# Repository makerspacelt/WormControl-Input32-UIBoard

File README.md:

---

WormControl Input32 User Interface board

NOTE: This is only a prototype now, so things might not work and everything might change 

Dev NOTE: before commit, run `./kibot.sh` to regenerate documentation, bom, gerbers and other assets.

* [schematics.pdf](gen/schematics.pdf)
* [pcb.pdf with dimensions](gen/pcb.pdf)
* [ibom.html](gen/single/ibom.html)

---

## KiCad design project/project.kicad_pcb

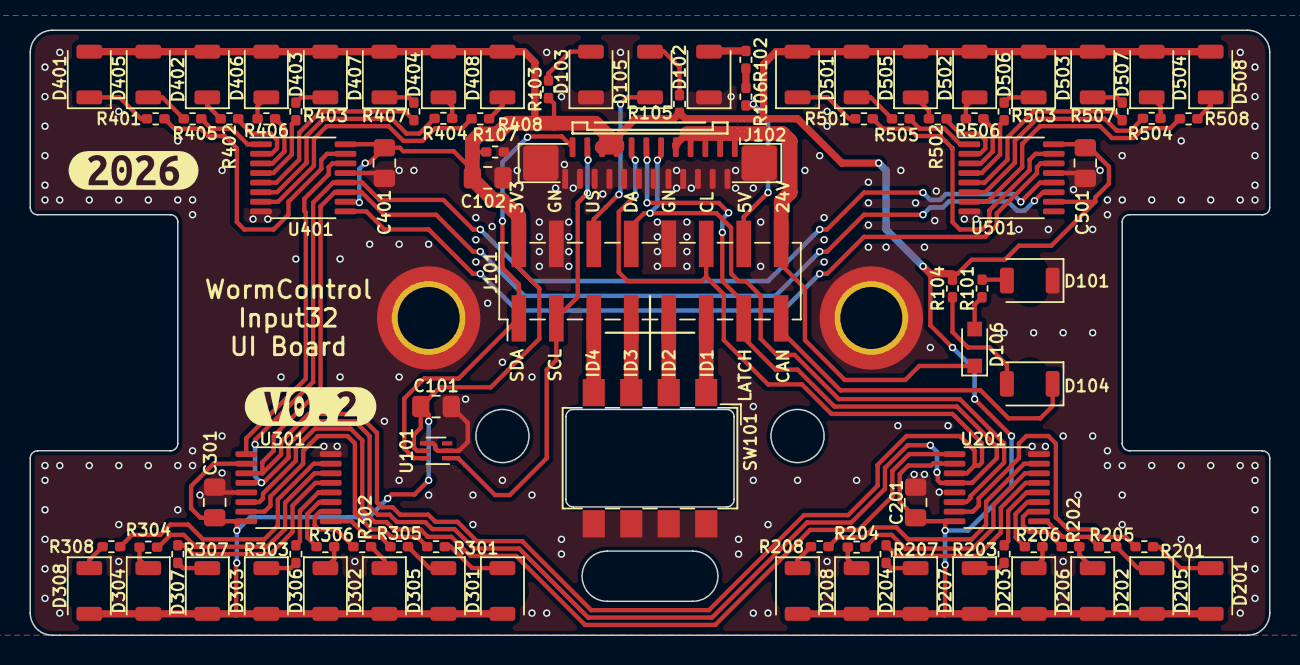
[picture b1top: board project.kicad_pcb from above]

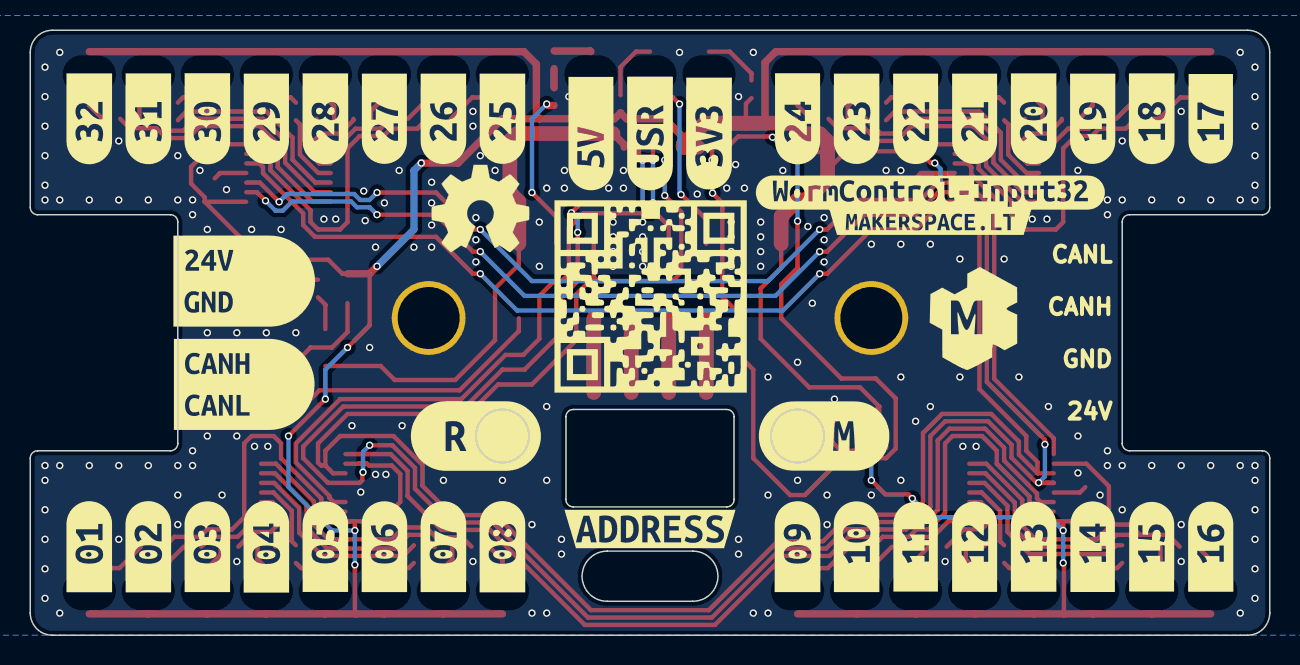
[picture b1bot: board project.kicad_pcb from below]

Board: 4 copper layers, 84.0 x 41.0 mm, 139 parts (44 on the bottom side), 89 nets.

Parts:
C101, C201, C301, C401, C501: 100n; C_0805_2012Metric_Pad1.18x1.45mm_HandSolder
C102: 22u/25v; C_0805_2012Metric_Pad1.18x1.45mm_HandSolder
D101, D102, D103, D104, D105, D201, D202, D203, D204, D205, D206, D207, D208, D301, D302, D303, D304, D305, D306, D307, D308, D401, D402, D403, D404, D405, D406, D407, D408, D501, D502, D503, D504, D505, D506, D507, D508: RED; LED_1206_3216Metric_ReverseMount
D106: 6V8; D_SOD-323_HandSoldering
G101: Logo_Open_Hardware_Large; OSHW-Symbol_6.7x6mm_SilkScreen
G102: LOGO_KMS; logo_kms_small_silkscreen
H101, H102: thread; post_m3x12.5mm
J101: Front; PinHeader_2x08_P2.54mm_Vertical_SMD
J102: FFC; AFC11-S24ICC-00
R101: 47k; R_0402_1005Metric_Pad0.72x0.64mm_HandSolder
R102, R103, R104, R105, R106: 4k7; R_0402_1005Metric_Pad0.72x0.64mm_HandSolder
R107, R201, R202, R203, R204, R205, R206, R207, R208, R301, R302, R303, R304, R305, R306, R307, R308, R401, R402, R403, R404, R405, R406, R407, R408, R501, R502, R503, R504, R505, R506, R507, R508: 330R; R_0402_1005Metric_Pad0.72x0.64mm_HandSolder
SW101: SW_DIP_x04; SW_DIP_SPSTx04_Slide_6.2x11.16mm_P2.54mm
U101: TMP102; SOT-563
U201, U301, U401, U501: 74HC595; TSSOP-16_4.4x5mm_P0.65mm
kibuzzard-69BC5702: G***; kibuzzard-69BC5702
kibuzzard-698AEBE9: G***; kibuzzard-698AEBE9
kibuzzard-67993A27: G***; kibuzzard-67993A27
kibuzzard-69823DD0: G***; kibuzzard-69823DD0
kibuzzard-69823DDF: G***; kibuzzard-69823DDF
kibuzzard-698182EE: G***; kibuzzard-698182EE
kibuzzard-698185E1: G***; kibuzzard-698185E1
kibuzzard-698187A9: G***; kibuzzard-698187A9
kibuzzard-698187B1: G***; kibuzzard-698187B1
kibuzzard-698187B8: G***; kibuzzard-698187B8
kibuzzard-698187BF: G***; kibuzzard-698187BF
kibuzzard-698187C6: G***; kibuzzard-698187C6
kibuzzard-698187CD: G***; kibuzzard-698187CD
kibuzzard-698187D5: G***; kibuzzard-698187D5
kibuzzard-698187DB: G***; kibuzzard-698187DB
kibuzzard-698187E9: G***; kibuzzard-698187E9
kibuzzard-698187FC: G***; kibuzzard-698187FC
kibuzzard-698188F7: G***; kibuzzard-698188F7
kibuzzard-6981864B: G***; kibuzzard-6981864B
kibuzzard-6981865C: G***; kibuzzard-6981865C
kibuzzard-6981866B: G***; kibuzzard-6981866B
kibuzzard-6981881E: G***; kibuzzard-6981881E
kibuzzard-6981882E: G***; kibuzzard-6981882E
kibuzzard-6981883F: G***; kibuzzard-6981883F
kibuzzard-6981885A: G***; kibuzzard-6981885A
kibuzzard-6981886F: G***; kibuzzard-6981886F
kibuzzard-6981888C: G***; kibuzzard-6981888C
kibuzzard-69818645: G***; kibuzzard-69818645
kibuzzard-69818664: G***; kibuzzard-69818664
kibuzzard-69818671: G***; kibuzzard-69818671
kibuzzard-69818678: G***; kibuzzard-69818678
kibuzzard-69818740: G***; kibuzzard-69818740
kibuzzard-69818775: G***; kibuzzard-69818775
kibuzzard-69818805: G***; kibuzzard-69818805
kibuzzard-69818826: G***; kibuzzard-69818826
kibuzzard-69818837: G***; kibuzzard-69818837
kibuzzard-69818852: G***; kibuzzard-69818852
kibuzzard-69818864: G***; kibuzzard-69818864
kibuzzard-69818879: G***; kibuzzard-69818879
kibuzzard-69818883: G***; kibuzzard-69818883
kibuzzard-69818905: G***; kibuzzard-69818905
kibuzzard-69818938: G***; kibuzzard-69818938
kibuzzard-69898103: G***; kibuzzard-69898103
kibuzzard-69898298: G***; kibuzzard-69898298

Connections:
3V3: C101.1, C102.1, C201.1, C301.1, C401.1, C501.1, D201.2 (A), D202.2 (A), D203.2 (A), D204.2 (A), D205.2 (A), D206.2 (A), D207.2 (A), D208.2 (A), D301.2 (A), D302.2 (A), D303.2 (A), D304.2 (A), D305.2 (A), D306.2 (A), D307.2 (A), D308.2 (A), D401.2 (A), D402.2 (A), D403.2 (A), D404.2 (A), D405.2 (A), D406.2 (A), D407.2 (A), D408.2 (A), D501.2 (A), D502.2 (A), D503.2 (A), D504.2 (A), D505.2 (A), D506.2 (A), D507.2 (A), D508.2 (A), J101.2, J102.17, J102.19, R103.1, R104.1, R105.1, R107.1, U101.5 (V+), U201.10 (~SRCLR), U201.16 (VCC), U301.10 (~SRCLR), U301.16 (VCC), U401.10 (~SRCLR), U401.16 (VCC), U501.10 (~SRCLR), U501.16 (VCC)
5V: J101.14, R106.1
24V: D106.1 (K), J101.16, J102.1, J102.3, J102.5, J102.7, J102.9
/data_1: U201.9 (QH'), U301.14 (SER)
/data_2: U301.9 (QH'), U401.14 (SER)
/data_3: U401.9 (QH'), U501.14 (SER)
/driver1/A: R201.2, U201.15 (QA)
/driver1/Ar: D201.1 (K), R201.1
/driver1/B: R205.2, U201.1 (QB)
/driver1/Br: D205.1 (K), R205.1
/driver1/C: R202.2, U201.2 (QC)
/driver1/Cr: D202.1 (K), R202.1
/driver1/D: R206.2, U201.3 (QD)
/driver1/Dr: D206.1 (K), R206.1
/driver1/E: R203.2, U201.4 (QE)
/driver1/Er: D203.1 (K), R203.1
/driver1/F: R207.2, U201.5 (QF)
/driver1/Fr: D207.1 (K), R207.1
/driver1/G: R204.2, U201.6 (QG)
/driver1/Gr: D204.1 (K), R204.1
/driver1/H: R208.2, U201.7 (QH)
/driver1/Hr: D208.1 (K), R208.1
/driver2/A: R301.2, U301.15 (QA)
/driver2/Ar: D301.1 (K), R301.1
/driver2/B: R305.2, U301.1 (QB)
/driver2/Br: D305.1 (K), R305.1
/driver2/C: R302.2, U301.2 (QC)
/driver2/Cr: D302.1 (K), R302.1
/driver2/D: R306.2, U301.3 (QD)
/driver2/Dr: D306.1 (K), R306.1
/driver2/E: R303.2, U301.4 (QE)
/driver2/Er: D303.1 (K), R303.1
/driver2/F: R307.2, U301.5 (QF)
/driver2/Fr: D307.1 (K), R307.1
/driver2/G: R304.2, U301.6 (QG)
/driver2/Gr: D304.1 (K), R304.1
/driver2/H: R308.2, U301.7 (QH)
/driver2/Hr: D308.1 (K), R308.1
/driver3/A: R401.2, U401.15 (QA)
/driver3/Ar: D401.1 (K), R401.1
/driver3/B: R405.2, U401.1 (QB)
/driver3/Br: D405.1 (K), R405.1
/driver3/C: R402.2, U401.2 (QC)
/driver3/Cr: D402.1 (K), R402.1
/driver3/D: R406.2, U401.3 (QD)
/driver3/Dr: D406.1 (K), R406.1
/driver3/E: R403.2, U401.4 (QE)
/driver3/Er: D403.1 (K), R403.1
/driver3/F: R407.2, U401.5 (QF)
/driver3/Fr: D407.1 (K), R407.1
/driver3/G: R404.2, U401.6 (QG)
/driver3/Gr: D404.1 (K), R404.1
/driver3/H: R408.2, U401.7 (QH)
/driver3/Hr: D408.1 (K), R408.1
/driver4/A: R501.2, U501.15 (QA)
/driver4/Ar: D501.1 (K), R501.1
/driver4/B: R505.2, U501.1 (QB)
/driver4/Br: D505.1 (K), R505.1
/driver4/C: R502.2, U501.2 (QC)
/driver4/Cr: D502.1 (K), R502.1
/driver4/D: R506.2, U501.3 (QD)
/driver4/Dr: D506.1 (K), R506.1
/driver4/E: R503.2, U501.4 (QE)
/driver4/Er: D503.1 (K), R503.1
/driver4/F: R507.2, U501.5 (QF)
/driver4/Fr: D507.1 (K), R507.1
/driver4/G: R504.2, U501.6 (QG)
/driver4/Gr: D504.1 (K), R504.1
/driver4/H: R508.2, U501.7 (QH)
/driver4/Hr: D508.1 (K), R508.1
CAN_LED: D104.1 (K), J101.15
CLOCK: J101.12, J102.15, U201.11 (SRCLK), U301.11 (SRCLK), U401.11 (SRCLK), U501.11 (SRCLK)
DATA: J101.8, J102.11, U201.14 (SER)
GND: C101.2, C102.2, C201.2, C301.2, C401.2, C501.2, D101.1 (K), D102.1 (K), D103.1 (K), H101.1, H102.1, J101.4, J101.10, J102.2, J102.4, J102.6, J102.8, J102.10, J102.12, J102.14, J102.16, J102.18, J102.20, J102.22, J102.24, J102.MP (MountPin), R107.2, SW101.5, SW101.6, SW101.7, SW101.8, U101.2 (GND), U101.4 (ADD0), U201.8 (GND), U201.13 (~OE), U301.8 (GND), U301.13 (~OE), U401.8 (GND), U401.13 (~OE), U501.8 (GND), U501.13 (~OE)
ID1: J101.11, SW101.1
ID2: J101.9, SW101.2
ID3: J101.7, SW101.3
ID4: J101.5, SW101.4
LATCH: J101.13, J102.13, U201.12 (RCLK), U301.12 (RCLK), U401.12 (RCLK), U501.12 (RCLK)
unnamed: D101.2 (A), R101.1
unnamed: D102.2 (A), R102.2
unnamed: D103.2 (A), R103.2
unnamed: D104.2 (A), R104.2
unnamed: D105.2 (A), R105.2
unnamed: D106.2 (A), R101.2
unnamed: R102.1, R106.2
SCL: J101.3, J102.21, U101.1 (SCL)
SDA: J101.1, J102.23, U101.6 (SDA)
USR_LED: D105.1 (K), J101.6

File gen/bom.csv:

"Row","Description","Part","References","Value","Footprint","Quantity Per PCB","Status","Datasheet","lcsc#","jlc-part-type"
"1","Unpolarized capacitor","C","C101,C201,C301,C401,C501","100n","C_0805_2012Metric_Pad1.18x1.45mm_HandSolder","5"," ","https://www.lcsc.com/datasheet/lcsc_datasheet_2304140030_Sam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","C28233","B"
"2","Unpolarized capacitor","C","C102","22u/25v","C_0805_2012Metric_Pad1.18x1.45mm_HandSolder","1"," ","https://www.lcsc.com/datasheet/lcsc_datasheet_2304140030_Sam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","C45783","B"
"3","Zener diode","D_Zener","D106","6V8","D_SOD-323_HandSoldering","1"," ","https://www.lcsc.com/datasheet/C123062.pdf","C123062","E"
"4","Light emitting diode","LED","D101,D102,D103,D104,D105,D201,D202,D203,D204,D205,D206,D207,D208,D301,D302,D303,D304,D305,D306,D307,D308,D401,D402,D403,D404,D405,D406,D407,D408,D501,D502,D503,D504,D505,D506,D507,D508","RED","LED_1206_3216Metric_ReverseMount","37"," ","https://www.lcsc.com/datasheet/lcsc_datasheet_2302091130_TOG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","C5356080","E"
"5","Generic connectable mounting pin connector, single row, 01x24, script generated (kicad-library-utils/schlib/autogen/connector/)","Conn_01x24_MountingPin","J102","FFC","AFC11-S24ICC-00","1"," ","https://www.lcsc.com/datasheet/lcsc_datasheet_2212161930_JUS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","C11075","E"
"6","Generic connector, single row, 01x16, script generated (kicad-library-utils/schlib/autogen/connector/)","Conn_01x16","J101","Front","PinHeader_2x08_P2.54mm_Vertical_SMD","1"," ","https://wmsc.lcsc.com/wmsc/upload/file/pdf/v2/lcsc/220914173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","C5160782","E"
"7","Resistor","R","R107,R201,R202,R203,R204,R205,R206,R207,R208,R301,R302,R303,R304,R305,R306,R307,R308,R401,R402,R403,R404,R405,R406,R407,R408,R501,R502,R503,R504,R505,R506,R507,R508","330R","R_0402_1005Metric_Pad0.72x0.64mm_HandSolder","33"," ","~","C25104","B"
"8","Resistor","R","R102,R103,R104,R105,R106","4k7","R_0402_1005Metric_Pad0.72x0.64mm_HandSolder","5"," ","~","C25900","B"
"9","Resistor","R","R101","47k","R_0402_1005Metric_Pad0.72x0.64mm_HandSolder","1"," ","~","C25792","B"
"10","4x DIP Switch, Single Pole Single Throw (SPST) switch, small symbol","SW_DIP_x04","SW101","SW_DIP_x04","SW_DIP_SPSTx04_Slide_6.2x11.16mm_P2.54mm","1"," ","https://www.lcsc.com/datasheet/lcsc_datasheet_2304140030_KAI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","C976366","E"
"11","8-bit serial in/out Shift Register 3-State Outputs","74HC595","U201,U301,U401,U501","74HC595","TSSOP-16_4.4x5mm_P0.65mm","4"," ","https://jlcpcb.com/api/file/downloadByFileSystemAccessId/859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","C20613246","E"
"12","Digital Temperature Sensor, +/- 3 °C, low-Power, SMBus, 12 bit, Two-Wire Serial Interface, SOT-563","TMP102xxDRL","U101","TMP102","SOT-563","1"," ","https://www.ti.com/lit/ds/symlink/tmp102.pdf","C99269","E"

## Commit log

2026-02-10 initial test version
2026-02-10 adding generated files
2026-02-10 fixing silkscreen typo
2026-02-10 fixing project info in all sheets
2026-02-12 updating kibot,fixing silkscreen, lowering led current
2026-03-19 parts consolidation and small fixes
    * Inverting input LEDs
    * Switching to TMP102 as TMP101 is no longer available
    * Helping 74HC forget state after power loss
    * bumping up version
2026-04-20 fixing tmp102 pinout
